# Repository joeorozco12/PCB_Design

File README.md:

# PCB Design: Analog Solutions

## Eagle CAD
Examples

## Altium 365: Circuit Maker
Examples

## Prototyping
Examples

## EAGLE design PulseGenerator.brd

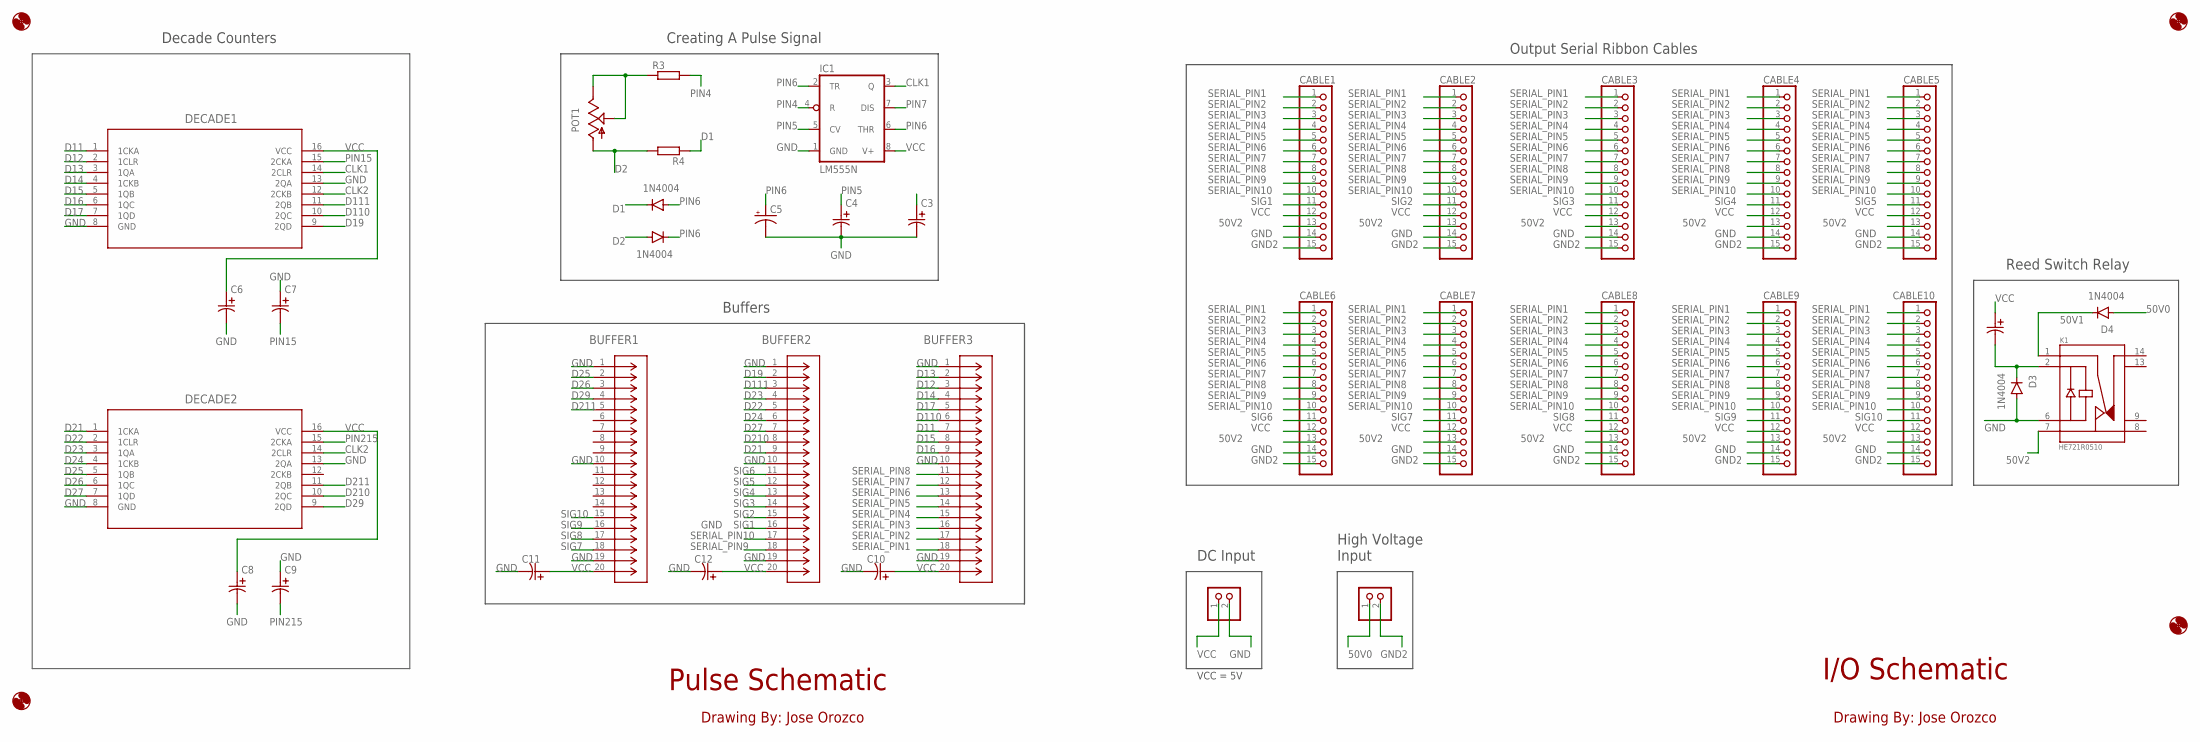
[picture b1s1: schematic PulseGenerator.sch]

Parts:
BUFFER1, BUFFER2, BUFFER3: 4820-3000-CP; CONN_3000_3MM
C1, C3, C4, C6, C7, C8, C9, C10, C11, C12: C322C104K5R5TA; CAP_C322_KEM
C5: CPOL-USTAP5-45; TAP5-45
CABLE1, CABLE2, CABLE3, CABLE4, CABLE5, CABLE6, CABLE7, CABLE8, CABLE9, CABLE10: PINHD-1X15; 1X15
D1, D2, D3, D4: 1N4004; DO41-10
DECADE1, DECADE2: SN74LS390N; N16
H1, H2, H3, H4: MOUNT-HOLE2.8; 2,8
IC1: LM555N; DIL08
JP1, JP2: PINHD-1X2; 1X02
K1: HE721R0510; RELAY_HE721R0510
POT1: TRIM_US-S63X; S63X
R3, R4: R-EU_0309/10; 0309/10

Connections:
50V0: D4.A, JP2.1
50V1: D4.C, K1.1
50V2: CABLE1.13, CABLE2.13, CABLE3.13, CABLE4.13, CABLE5.13, CABLE6.13, CABLE7.13, CABLE8.13, CABLE9.13, CABLE10.13, K1.7
CLK1: DECADE1.14 (2CLR), IC1.3 (Q)
CLK2: DECADE1.12 (2CKB), DECADE2.14 (2CLR)
D1: D1.C, R4.1
D2: D2.A, POT1.A, R4.2
D11: BUFFER3.7, DECADE1.1 (1CKA)
D12: BUFFER3.3, DECADE1.2 (1CLR)
D13: BUFFER3.2, DECADE1.3 (1QA)
D14: BUFFER3.4, DECADE1.4 (1CKB)
D15: BUFFER3.8, DECADE1.5 (1QB)
D16: BUFFER3.9, DECADE1.6 (1QC)
D17: BUFFER3.5, DECADE1.7 (1QD)
D19: BUFFER2.2, DECADE1.9 (2QD)
D21: BUFFER2.9, DECADE2.1 (1CKA)
D22: BUFFER2.5, DECADE2.2 (1CLR)
D23: BUFFER2.4, DECADE2.3 (1QA)
D24: BUFFER2.6, DECADE2.4 (1CKB)
D25: BUFFER1.2, DECADE2.5 (1QB)
D26: BUFFER1.3, DECADE2.6 (1QC)
D27: BUFFER2.7, DECADE2.7 (1QD)
D29: BUFFER1.4, DECADE2.9 (2QD)
D110: BUFFER3.6, DECADE1.10 (2QC)
D111: BUFFER2.3, DECADE1.11 (2QB)
D210: BUFFER2.8, DECADE2.10 (2QC)
D211: BUFFER1.5, DECADE2.11 (2QB)
GND: BUFFER1.1, BUFFER1.10, BUFFER1.19, BUFFER2.1, BUFFER2.10, BUFFER2.19, BUFFER3.1, BUFFER3.10, BUFFER3.19, C3.2, C4.2, C5.-, C6.2, C7.1, C8.2, C9.1, C10.2, C11.2, C12.2, CABLE1.14, CABLE2.14, CABLE3.14, CABLE4.14, CABLE5.14, CABLE6.14, CABLE7.14, CABLE8.14, CABLE9.14, CABLE10.14, D3.A, DECADE1.8 (GND), DECADE1.13 (2QA), DECADE2.8 (GND), DECADE2.13 (2QA), IC1.1 (GND), JP1.2, K1.6
GND2: CABLE1.15, CABLE2.15, CABLE3.15, CABLE4.15, CABLE5.15, CABLE6.15, CABLE7.15, CABLE8.15, CABLE9.15, CABLE10.15, JP2.2
unnamed: POT1.E, POT1.S, R3.1
unnamed: C1.2, D3.C, K1.2
PIN4: IC1.4 (R), R3.2
PIN5: C4.1, IC1.5 (CV)
PIN6: C5.+, D1.A, D2.C, IC1.2 (TR), IC1.6 (THR)
PIN7: IC1.7 (DIS)
PIN15: C7.2, DECADE1.15 (2CKA)
PIN215: C9.2, DECADE2.15 (2CKA)
SERIAL_PIN1: BUFFER3.18, CABLE1.1, CABLE2.1, CABLE3.1, CABLE4.1, CABLE5.1, CABLE6.1, CABLE7.1, CABLE8.1, CABLE9.1, CABLE10.1
SERIAL_PIN2: BUFFER3.17, CABLE1.2, CABLE2.2, CABLE3.2, CABLE4.2, CABLE5.2, CABLE6.2, CABLE7.2, CABLE8.2, CABLE9.2, CABLE10.2
SERIAL_PIN3: BUFFER3.16, CABLE1.3, CABLE2.3, CABLE3.3, CABLE4.3, CABLE5.3, CABLE6.3, CABLE7.3, CABLE8.3, CABLE9.3, CABLE10.3
SERIAL_PIN4: BUFFER3.15, CABLE1.4, CABLE2.4, CABLE3.4, CABLE4.4, CABLE5.4, CABLE6.4, CABLE7.4, CABLE8.4, CABLE9.4, CABLE10.4
SERIAL_PIN5: BUFFER3.14, CABLE1.5, CABLE2.5, CABLE3.5, CABLE4.5, CABLE5.5, CABLE6.5, CABLE7.5, CABLE8.5, CABLE9.5, CABLE10.5
SERIAL_PIN6: BUFFER3.13, CABLE1.6, CABLE2.6, CABLE3.6, CABLE4.6, CABLE5.6, CABLE6.6, CABLE7.6, CABLE8.6, CABLE9.6, CABLE10.6
SERIAL_PIN7: BUFFER3.12, CABLE1.7, CABLE2.7, CABLE3.7, CABLE4.7, CABLE5.7, CABLE6.7, CABLE7.7, CABLE8.7, CABLE9.7, CABLE10.7
SERIAL_PIN8: BUFFER3.11, CABLE1.8, CABLE2.8, CABLE3.8, CABLE4.8, CABLE5.8, CABLE6.8, CABLE7.8, CABLE8.8, CABLE9.8, CABLE10.8
SERIAL_PIN9: BUFFER2.18, CABLE1.9, CABLE2.9, CABLE3.9, CABLE4.9, CABLE5.9, CABLE6.9, CABLE7.9, CABLE8.9, CABLE9.9, CABLE10.9
SERIAL_PIN10: BUFFER2.17, CABLE1.10, CABLE2.10, CABLE3.10, CABLE4.10, CABLE5.10, CABLE6.10, CABLE7.10, CABLE8.10, CABLE9.10, CABLE10.10
SIG1: BUFFER2.16, CABLE1.11
SIG2: BUFFER2.15, CABLE2.11
SIG3: BUFFER2.14, CABLE3.11
SIG4: BUFFER2.13, CABLE4.11
SIG5: BUFFER2.12, CABLE5.11
SIG6: BUFFER2.11, CABLE6.11
SIG7: BUFFER1.18, CABLE7.11
SIG8: BUFFER1.17, CABLE8.11
SIG9: BUFFER1.16, CABLE9.11
SIG10: BUFFER1.15, CABLE10.11
VCC: BUFFER1.20, BUFFER2.20, BUFFER3.20, C1.1, C6.1, C8.1, C10.1, C11.1, C12.1, CABLE1.12, CABLE2.12, CABLE3.12, CABLE4.12, CABLE5.12, CABLE6.12, CABLE7.12, CABLE8.12, CABLE9.12, CABLE10.12, DECADE1.16 (VCC), DECADE2.16 (VCC), IC1.8 (V+), JP1.1

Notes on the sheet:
Creating A Pulse Signal
Decade Counters
DC Input
VCC = 5V
Buffers
Output Serial Ribbon Cables
High Voltage Input
Reed Switch Relay
Drawing By: Jose Orozco
I/O Schematic
Pulse Schematic

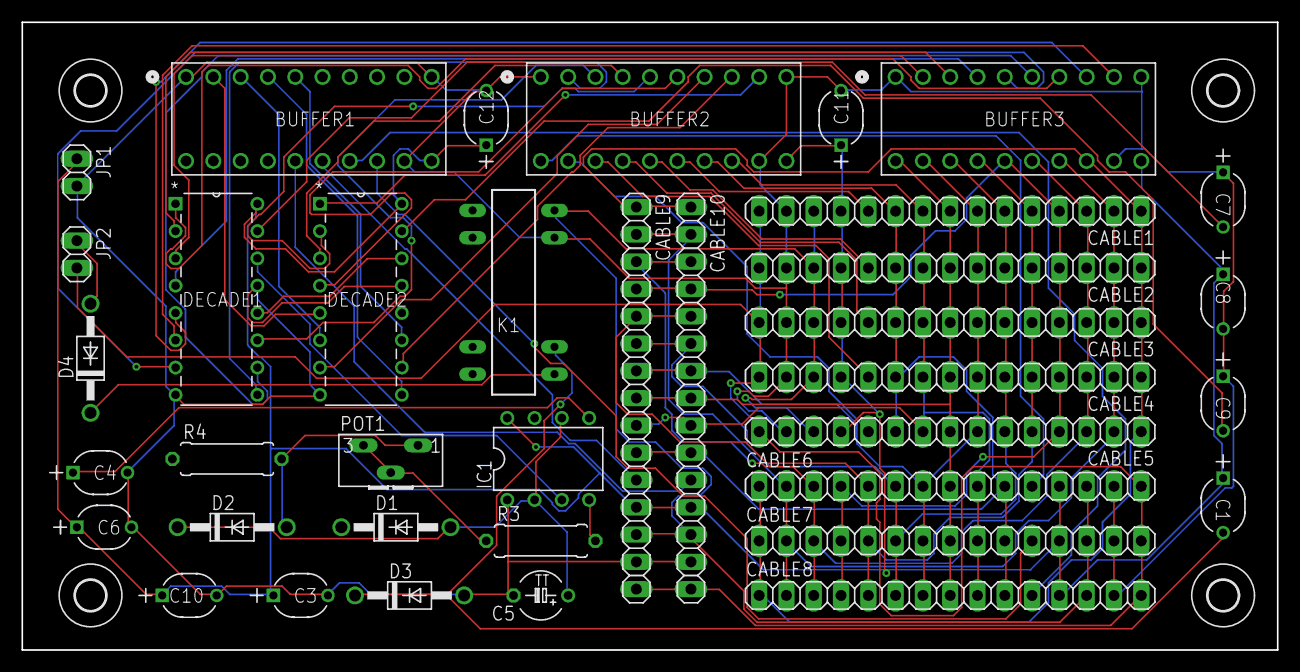
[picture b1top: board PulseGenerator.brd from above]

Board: 2 copper layers, 116.8 x 58.4 mm, 41 parts (0 on the bottom side), 57 nets.

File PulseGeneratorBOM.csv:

"Qty";"Value";"Device";"Package";"Parts";"Description";"BUILT_BY";"COPYRIGHT";"DATASHEET_URL";"DESCRIPTION";"FAMILY_NAME";"GENERIC_PART_NUMBER";"INDUSTRY_STD_PKG_TYPE";"MANUFACTURER";"MANUFACTURER_PART_NUMBER";"PACKAGE_DESIGNATOR";"PIN_COUNT";"POPULARITY";"SOURCELIBRARY";"SPICEPREFIX";"VENDOR";
"1";"";"3RP/1610N";"3RP/1610N";"POT1";"16mm Potentiometer one level";"";"";"";"";"";"";"";"";"";"";"";"8";"";"";"";
"1";"";"CPOL-USTAP5-45";"TAP5-45";"C5";"POLARIZED CAPACITOR, American symbol";"";"";"";"";"";"";"";"";"";"";"";"1";"";"C";"";
"10";"";"PINHD-1X15";"1X15";"CABLE1, CABLE2, CABLE3, CABLE4, CABLE5, CABLE6, CABLE7, CABLE8, CABLE9, CABLE10";"PIN HEADER";"";"";"";"";"";"";"";"";"";"";"";"4";"";"";"";
"2";"";"PINHD-1X2";"1X02";"JP1, JP2";"PIN HEADER";"";"";"";"";"";"";"";"";"";"";"";"98";"";"";"";
"2";"";"R-EU_0309/10";"0309/10";"R3, R4";"RESISTOR, European symbol";"";"";"";"";"";"";"";"";"";"";"";"2";"";"R";"";
"2";"1N4004";"1N4004";"DO41-10";"D1, D2";"DIODE";"";"";"";"";"";"";"";"";"";"";"";"82";"";"";"";
"3";"4820-3000-CP";"4820-3000-CP";"CONN_3000_3MM";"BUFFER1, BUFFER2, BUFFER3";"";"EMA_Matt";"Copyright (C) 2018 Accelerated Designs. All rights reserved";"";"";"";"";"";"";"4820-3000-CP";"";"";"";"3M_2019-10-11";"";"3M";
"9";"C322C104K5R5TA";"C322C104K5R5TA";"CAP_C322_KEM";"C3, C4, C6, C7, C8, C9, C10, C11, C12";"";"EMA_UL_Team";"";"";"";"";"";"";"";"C322C104K5R5TA";"";"";"";"Kemet_2012-08-08";"";"Kemet";
"1";"LM555N";"LM555N";"DIL08";"IC1";"TIMER";"";"";"";"";"";"";"";"";"";"";"";"0";"";"";"";
"4";"MOUNT-HOLE2.8";"MOUNT-HOLE2.8";"2,8";"H1, H2, H3, H4";"MOUNTING HOLE with drill center marker";"";"";"";"";"";"";"";"";"";"";"";"15";"";"";"";
"2";"SN74LS390N";"SN74LS390N";"N16";"DECADE1, DECADE2";"";"";"";"http://www.ti.com/lit/gpn/SN74LS390";"Dual 4-Bit Decade Counters";"DECADE COUNTER";"SN74LS390";"PDIP";"Texas Instruments";"";"N";"16";"";"";"";"";

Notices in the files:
parts and their libraries:
COPYRIGHT: Copyright (C) 2018 Accelerated Designs. All rights reserved
